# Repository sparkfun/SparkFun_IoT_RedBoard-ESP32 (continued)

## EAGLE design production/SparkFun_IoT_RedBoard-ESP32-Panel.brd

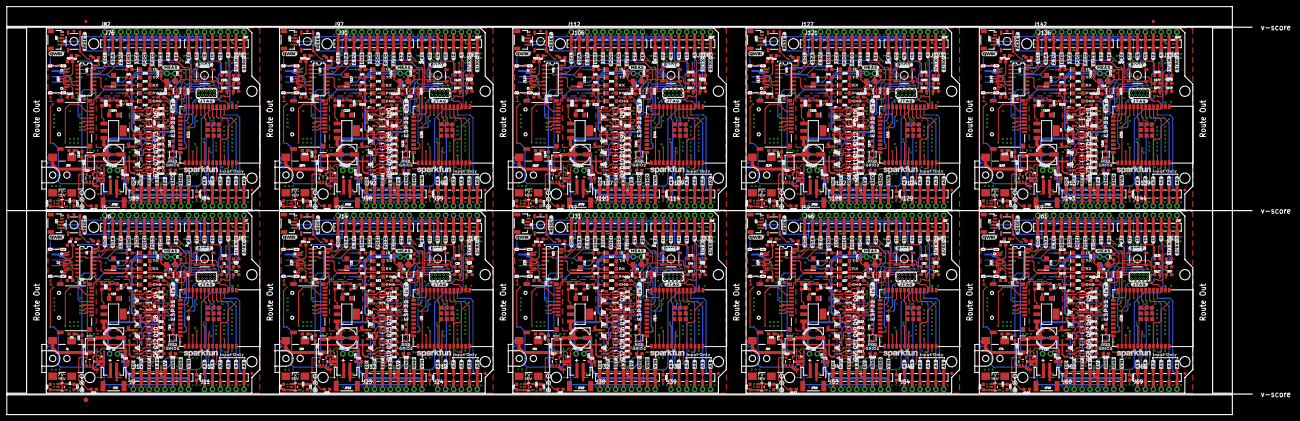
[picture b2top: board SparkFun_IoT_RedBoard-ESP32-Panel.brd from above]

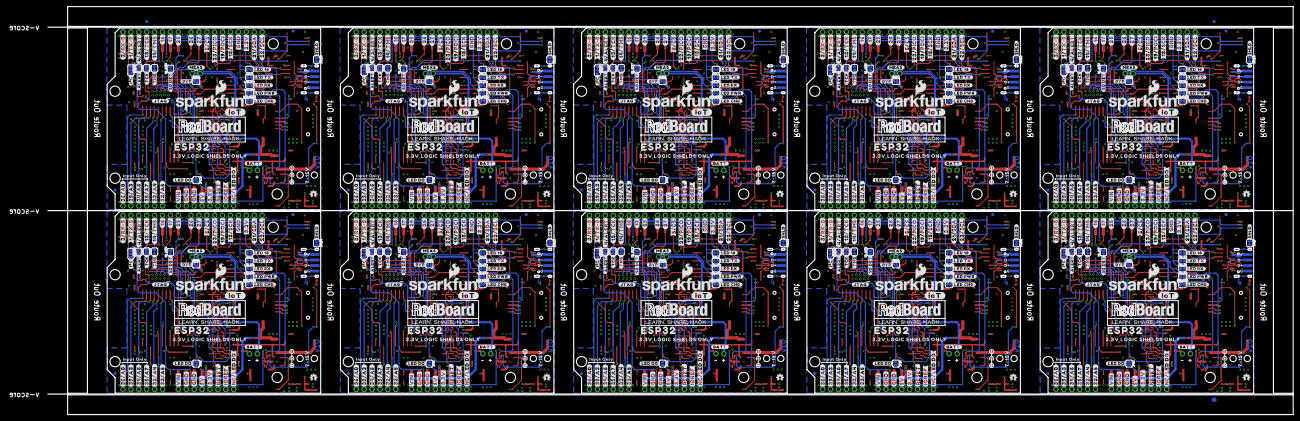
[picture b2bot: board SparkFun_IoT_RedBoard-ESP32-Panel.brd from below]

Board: 4 copper layers, 400.1 x 131.1 mm, 2336 parts (813 on the bottom side), 840 nets.

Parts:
!ALERT!, !ALERT!1, !ALERT!2, !ALERT!3, !ALERT!4, !ALERT!5, !ALERT!6, !ALERT!7, !ALERT!8, !ALERT!9: JUMPER-SMT_2_NO_SILK; SMT-JUMPER_2_NO_SILK
BYP, BYP1, BYP2, BYP3, BYP4, BYP5, BYP6, BYP7, BYP8, BYP9: JUMPER-SMT_2_NO_SILK; SMT-JUMPER_2_NO_SILK
C1, C2, C4, C5, C7, C11, C12, C13, C14, C17, C18, C20, C21, C24, C25, C26, C29, C31, C32, C35, C36, C37, C39, C40, C43, C44, C45, C48, C50, C51, C54, C55, C56, C58, C59, C62, C63, C64, C67, C69, C70, C73, C74, C75, C77, C78, C81, C82, C83, C86, C88, C89, C92, C93, C94, C96, C97, C100, C101, C102, C105, C107, C108, C111, C112, C113, C115, C116, C119, C120, C121, C124, C126, C127, C130, C131, C132, C134, C135, C138, C139, C140, C143, C145, C146, C149, C150, C151, C153, C154, C157, C158, C159, C162, C164, C165, C168, C169, C170, C172, C173, C176, C177, C178, C181, C183, C184, C187, C188, C189: 0.1uF; 0603
C3, C19, C27, C38, C46, C57, C65, C76, C84, C95, C103, C114, C122, C133, C141, C152, C160, C171, C179, C190: 10uF; 0603
C6, C10, C22, C28, C41, C47, C60, C66, C79, C85, C98, C104, C117, C123, C136, C142, C155, C161, C174, C180: 10uF; EIA3216
C8, C23, C42, C61, C80, C99, C118, C137, C156, C175: 10nF; 0603
C9, C30, C49, C68, C87, C106, C125, C144, C163, C182: 47uF; PANASONIC_D
C15, C16, C33, C34, C52, C53, C71, C72, C90, C91, C109, C110, C128, C129, C147, C148, C166, C167, C185, C186: 4.7uF; 0603
D1, D11, D18, D25, D32, D39, D46, D53, D60, D67: 3A/40V/500mV; SMA-DIODE
D2, D8, D15, D22, D29, D36, D43, D50, D57, D64: GREEN; LED-1206
D3, D4, D9, D12, D16, D19, D23, D26, D30, D33, D37, D40, D44, D47, D51, D54, D58, D61, D65, D68: Yellow; LED-1206
D5, D13, D20, D27, D34, D41, D48, D55, D62, D69: RED; LED-1206
D6, D10, D17, D24, D31, D38, D45, D52, D59, D66: BLUE; LED-1206
D7, D14, D21, D28, D35, D42, D49, D56, D63, D70: WS2812_2020; WS2812-2020
DOOT, DOOT1, DOOT2, DOOT3, DOOT4, DOOT5, DOOT6, DOOT7, DOOT8, DOOT9: GPIO0; TACTILE_SWITCH_SMD_5.2MM
E$1, E$2, E$3, E$4: FIDUCIAL-1X2
E$5, E$6: FIDUCIAL-1.5X3
F1, F2, F3, F4, F5, F6, F7, F8, F9, F10: 6V/0.75A/1.5A; 1206
I2C, I2C1, I2C2, I2C3, I2C4, I2C5, I2C6, I2C7, I2C8, I2C9: JUMPER-SMT_3_2-NC_TRACE_SILK; SMT-JUMPER_3_2-NC_TRACE_SILK
J1, J29, J44, J59, J74, J89, J104, J119, J134, J149: 5.5x2.1mm Barrel; POWER_JACK_SMD
J2, J20, J35, J50, J65, J80, J95, J110, J125, J140: USB-C; USB-C-16P-4LAYER-ISOLATED
J3, J21, J36, J51, J66, J81, J96, J111, J126, J141: USB_SOLDER_PADS; USB-SOLDER-PADS
J4, J26, J41, J56, J71, J86, J101, J116, J131, J146: 2X5_PTH_SILK_.05
J5, J22, J37, J52, J67, J82, J97, J112, J127, J142: M10NO_SILK; 1X10_NO_SILK
J6, J14, J31, J46, J61, J76, J91, J106, J121, J136: 1X10_SMD_COMBINED
J7, J9, J23, J25, J38, J40, J53, J55, J68, J70, J83, J85, J98, J100, J113, J115, J128, J130, J143, J145: 1X08_NO_SILK
J8, J10, J17, J18, J32, J33, J47, J48, J62, J63, J77, J78, J92, J93, J107, J108, J122, J123, J137, J138: 1X08_SMD_COMBINED
J11, J24, J39, J54, J69, J84, J99, J114, J129, J144: 1X06_NO_SILK
J12, J19, J34, J49, J64, J79, J94, J109, J124, J139: 1X06_SMD_STRAIGHT_COMBO
J13, J27, J42, J57, J72, J87, J102, J117, J132, J147: QWIIC_RIGHT_ANGLE; JST04_1MM_RA
J15, J28, J43, J58, J73, J88, J103, J118, J133, J148: MICRO-SD-PUSH-PUSH-EXT-PIN; MICROSD-EXTERNALPIN
J16, J30, J45, J60, J75, J90, J105, J120, J135, J150: 1X02_NO_SILK
JP1, JP7, JP8, JP9, JP15, JP16, JP17, JP18, JP25, JP26, JP27, JP28, JP35, JP36, JP37, JP38, JP45, JP46, JP47, JP48, JP55, JP56, JP57, JP58, JP65, JP66, JP67, JP68, JP75, JP76, JP77, JP78, JP85, JP86, JP87, JP88, JP95, JP96, JP97, JP98: FIDUCIAL1X2; FIDUCIAL-1X2
JP2, JP19, JP29, JP39, JP49, JP59, JP69, JP79, JP89, JP99: LiPo; JST-2-SMD
JP3, JP4, JP5, JP6, JP11, JP12, JP13, JP14, JP21, JP22, JP23, JP24, JP31, JP32, JP33, JP34, JP41, JP42, JP43, JP44, JP51, JP52, JP53, JP54, JP61, JP62, JP63, JP64, JP71, JP72, JP73, JP74, JP81, JP82, JP83, JP84, JP91, JP92, JP93, JP94: STAND-OFF
JP10, JP20, JP30, JP40, JP50, JP60, JP70, JP80, JP90, JP100: LED_DO; SMT-JUMPER_2_NO_SILK
LED_1, LED_2, LED_3, LED_4, LED_5, LED_6, LED_7, LED_8, LED_9, LED_18: JUMPER-SMT_2_NC_TRACE_SILK; SMT-JUMPER_2_NC_TRACE_SILK
LED_CHG, LED_CHG1, LED_CHG2, LED_CHG3, LED_CHG4, LED_CHG5, LED_CHG6, LED_CHG7, LED_CHG8, LED_CHG9: JUMPER-SMT_2_NC_TRACE_SILK; SMT-JUMPER_2_NC_TRACE_SILK
LED_PWR, LED_PWR1, LED_PWR2, LED_PWR3, LED_PWR4, LED_PWR5, LED_PWR6, LED_PWR7, LED_PWR8, LED_PWR9: JUMPER-SMT_2_NC_TRACE_SILK; SMT-JUMPER_2_NC_TRACE_SILK
LED_RX, LED_RX1, LED_RX2, LED_RX3, LED_RX4, LED_RX5, LED_RX6, LED_RX7, LED_RX8, LED_RX9: JUMPER-SMT_2_NC_TRACE_SILK; SMT-JUMPER_2_NC_TRACE_SILK
LED_TX, LED_TX1, LED_TX2, LED_TX3, LED_TX4, LED_TX5, LED_TX6, LED_TX7, LED_TX8, LED_TX9: JUMPER-SMT_2_NC_TRACE_SILK; SMT-JUMPER_2_NC_TRACE_SILK
LOGO1, LOGO4, LOGO9, LOGO13, LOGO17, LOGO21, LOGO25, LOGO29, LOGO33, LOGO37: SFE_LOGO_NAME.1_INCH; SFE_LOGO_NAME_.1
LOGO2, LOGO5, LOGO10, LOGO14, LOGO18, LOGO22, LOGO26, LOGO30, LOGO34, LOGO38: QWIIC_LOGO_5MM; QWIIC_5MM
LOGO3, LOGO7, LOGO11, LOGO15, LOGO19, LOGO23, LOGO27, LOGO31, LOGO35, LOGO39: OSHW-LOGOMINI; OSHW-LOGO-MINI
LOGO6, LOGO8, LOGO12, LOGO16, LOGO20, LOGO24, LOGO28, LOGO32, LOGO36, LOGO40: SFE_LOGO_NAME_FLAME.2_INCH; SFE_LOGO_NAME_FLAME_.2
MEAS, MEAS1, MEAS2, MEAS3, MEAS4, MEAS5, MEAS6, MEAS7, MEAS8, MEAS9: JUMPER-COMBO_2_NC_TRACE; COMBO-JUMPER_2_NC_TRACE
Q1, Q14, Q27, Q40, Q53, Q66, Q79, Q92, Q105, Q118: MBT3904DW1T1; SC70-6
Q2, Q17, Q30, Q43, Q56, Q69, Q82, Q95, Q108, Q121: SC70-6
Q3, Q5, Q7, Q9, Q11, Q13, Q16, Q18, Q20, Q22, Q24, Q26, Q29, Q31, Q33, Q35, Q37, Q39, Q42, Q44, Q46, Q48, Q50, Q52, Q55, Q57, Q59, Q61, Q63, Q65, Q68, Q70, Q72, Q74, Q76, Q78, Q81, Q83, Q85, Q87, Q89, Q91, Q94, Q96, Q98, Q100, Q102, Q104, Q107, Q109, Q111, Q113, Q115, Q117, Q120, Q122, Q124, Q126, Q128, Q130: 20V/4.2A/52mΩ/1.4W; SOT23-3
Q4, Q6, Q8, Q10, Q12, Q15, Q19, Q21, Q23, Q25, Q28, Q32, Q34, Q36, Q38, Q41, Q45, Q47, Q49, Q51, Q54, Q58, Q60, Q62, Q64, Q67, Q71, Q73, Q75, Q77, Q80, Q84, Q86, Q88, Q90, Q93, Q97, Q99, Q101, Q103, Q106, Q110, Q112, Q114, Q116, Q119, Q123, Q125, Q127, Q129: SOT363_PHILIPS
R1, R6, R7, R12, R13, R14, R15, R23, R35, R36, R37, R43, R45, R46, R47, R58, R65, R66, R67, R73, R75, R76, R77, R88, R95, R96, R97, R103, R105, R106, R107, R118, R125, R126, R127, R133, R135, R136, R137, R148, R155, R156, R157, R163, R165, R166, R167, R178, R185, R186, R187, R193, R195, R196, R197, R208, R215, R216, R217, R223, R225, R226, R227, R238, R245, R246, R247, R253, R255, R256, R257, R268, R275, R276, R277, R283, R285, R286, R287, R298: 10k; 0603
R2, R3, R33, R34, R63, R64, R93, R94, R123, R124, R153, R154, R183, R184, R213, R214, R243, R244, R273, R274: 5.1k; 0603
R4, R5, R21, R31, R32, R52, R61, R62, R82, R91, R92, R112, R121, R122, R142, R151, R152, R172, R181, R182, R202, R211, R212, R232, R241, R242, R262, R271, R272, R292: 1k; 0603
R8, R28, R29, R39, R40, R59, R69, R70, R89, R99, R100, R119, R129, R130, R149, R159, R160, R179, R189, R190, R209, R219, R220, R239, R249, R250, R269, R279, R280, R299: 2.2k; 0603
R9, R38, R68, R98, R128, R158, R188, R218, R248, R278: 4.7k; 0603
R10, R42, R72, R102, R132, R162, R192, R222, R252, R282: 240; 0603
R11, R41, R71, R101, R131, R161, R191, R221, R251, R281: 715; 0603
R16, R44, R74, R104, R134, R164, R194, R224, R254, R284: 47k; 0603
R17, R19, R24, R26, R48, R50, R54, R56, R78, R80, R84, R86, R108, R110, R114, R116, R138, R140, R144, R146, R168, R170, R174, R176, R198, R200, R204, R206, R228, R230, R234, R236, R258, R260, R264, R266, R288, R290, R294, R296: 100k; 0603
R18, R20, R25, R27, R49, R51, R55, R57, R79, R81, R85, R87, R109, R111, R115, R117, R139, R141, R145, R147, R169, R171, R175, R177, R199, R201, R205, R207, R229, R231, R235, R237, R259, R261, R265, R267, R289, R291, R295, R297: 1M; 0603
R22, R53, R83, R113, R143, R173, R203, R233, R263, R293: 2.0k; 0603
R30, R60, R90, R120, R150, R180, R210, R240, R270, R300: 100; 0603
S1, S2, S3, S4, S5, S6, S7, S8, S9, S10: Reset; TACTILE_SWITCH_SMD_5.2MM
SD_DET, SD_DET1, SD_DET2, SD_DET3, SD_DET4, SD_DET5, SD_DET6, SD_DET7, SD_DET8, SD_DET9: SD_DET; SMT-JUMPER_2_NO_SILK
SHLD, SHLD1, SHLD2, SHLD3, SHLD4, SHLD5, SHLD6, SHLD7, SHLD8, SHLD9: SHLD; SMT-JUMPER_2_NC_TRACE_SILK
TCK, TCK1, TCK2, TCK3, TCK4, TCK5, TCK6, TCK7, TCK8, TCK9: JUMPER-SMT_2_NC_TRACE_SILK; SMT-JUMPER_2_NC_TRACE_SILK
TMS, TMS1, TMS2, TMS3, TMS4, TMS5, TMS6, TMS7, TMS8, TMS9: JUMPER-SMT_2_NC_TRACE_SILK; SMT-JUMPER_2_NC_TRACE_SILK
TP1, TP2, TP3, TP4, TP5, TP6, TP7, TP8, TP9, TP10: TEST-POINT3; PAD.03X.03
U1, U8, U14, U20, U26, U32, U38, U44, U50, U56: ESP-WROOM-3232D; ESP-WROOM-32D
U2, U7, U13, U19, U25, U31, U37, U43, U49, U55: CH340C; SO016
U3, U9, U15, U21, U27, U33, U39, U45, U51, U57: LM1117; SOT223
U4, U10, U16, U22, U28, U34, U40, U46, U52, U58: XC6222B331MR-G; SOT23-5
U5, U11, U17, U23, U29, U35, U41, U47, U53, U59: MCP73831; SOT23-5
U6, U12, U18, U24, U30, U36, U42, U48, U54, U60: MAX17048; DFN-8
U$1, U$87, U$225, U$337, U$449, U$561, U$673, U$785, U$897, U$1009: V323252
U$2, U$3, U$226, U$338, U$450, U$562, U$674, U$786, U$898, U$1010: #SCL#34
U$4, U$95, U$227, U$339, U$451, U$563, U$675, U$787, U$899, U$1011: #SDA#33
U$5, U$116, U$228, U$340, U$452, U$564, U$676, U$788, U$900, U$1012: #3#3V#33
U$6, U$117, U$229, U$341, U$453, U$565, U$677, U$789, U$901, U$1013: #GND#32
U$7, U$118, U$230, U$342, U$454, U$566, U$678, U$790, U$902, U$1014: #SCK#31
U$8, U$119, U$231, U$343, U$455, U$567, U$679, U$791, U$903, U$1015: #POCI#30
U$9, U$120, U$232, U$344, U$456, U$568, U$680, U$792, U$904, U$1016: #PICO#29
U$10, U$121, U$233, U$345, U$457, U$569, U$681, U$793, U$905, U$1017: 1836
U$11, U$42, U$150, U$208, U$262, U$320, U$374, U$432, U$486, U$544, U$598, U$656, U$710, U$768, U$822, U$880, U$934, U$992, U$1046, U$1104: #MEAS#1851
U$12, U$122, U$234, U$346, U$458, U$570, U$682, U$794, U$906, U$1018: #27#27
U$13, U$123, U$235, U$347, U$459, U$571, U$683, U$795, U$907, U$1019: #26#26
U$14, U$124, U$236, U$348, U$460, U$572, U$684, U$796, U$908, U$1020: TX1838
U$15, U$125, U$237, U$349, U$461, U$573, U$685, U$797, U$909, U$1021: RX1839
U$16, U$126, U$238, U$350, U$462, U$574, U$686, U$798, U$910, U$1022: PWR1837
U$17, U$127, U$239, U$351, U$463, U$575, U$687, U$799, U$911, U$1023: CHG1840
U$18, U$128, U$240, U$352, U$464, U$576, U$688, U$800, U$912, U$1024: #25#18
U$19, U$129, U$241, U$353, U$465, U$577, U$689, U$801, U$913, U$1025: #17#17
U$20, U$130, U$242, U$354, U$466, U$578, U$690, U$802, U$914, U$1026: #16#15
U$21, U$131, U$243, U$355, U$467, U$579, U$691, U$803, U$915, U$1027: #14#14
U$22, U$132, U$244, U$356, U$468, U$580, U$692, U$804, U$916, U$1028: #13#5
U$23, U$133, U$245, U$357, U$469, U$581, U$693, U$805, U$917, U$1029: #4#2
U$24, U$202, U$314, U$426, U$538, U$650, U$762, U$874, U$986, U$1098: #3#RX#0#4
U$25, U$199, U$311, U$423, U$535, U$647, U$759, U$871, U$983, U$1095: #3#RX#0#0
U$26, U$134, U$246, U$358, U$470, U$582, U$694, U$806, U$918, U$1030: #RESET#1842
U$27, U$135, U$247, U$359, U$471, U$583, U$695, U$807, U$919, U$1031: #BOOT#1841
U$28, U$46, U$136, U$154, U$248, U$266, U$360, U$378, U$472, U$490, U$584, U$602, U$696, U$714, U$808, U$826, U$920, U$938, U$1032, U$1050: #JTAG#1847
U$29, U$137, U$249, U$361, U$473, U$585, U$697, U$809, U$921, U$1033: #A0#1843
U$30, U$138, U$250, U$362, U$474, U$586, U$698, U$810, U$922, U$1034: #A3#1843
U$31, U$139, U$251, U$363, U$475, U$587, U$699, U$811, U$923, U$1035: #A6#1843
U$32, U$140, U$252, U$364, U$476, U$588, U$700, U$812, U$924, U$1036: #A7#1843
U$33, U$141, U$253, U$365, U$477, U$589, U$701, U$813, U$925, U$1037: #A4#1843
U$34, U$142, U$254, U$366, U$478, U$590, U$702, U$814, U$926, U$1038: #A5#1843
U$35, U$143, U$255, U$367, U$479, U$591, U$703, U$815, U$927, U$1039: #VIN#1843
U$36, U$37, U$144, U$145, U$256, U$257, U$368, U$369, U$480, U$481, U$592, U$593, U$704, U$705, U$816, U$817, U$928, U$929, U$1040, U$1041: #GND#1844
U$38, U$146, U$258, U$370, U$482, U$594, U$706, U$818, U$930, U$1042: #5V#1845
U$39, U$147, U$259, U$371, U$483, U$595, U$707, U$819, U$931, U$1043: #3#3V#1845
U$40, U$148, U$260, U$372, U$484, U$596, U$708, U$820, U$932, U$1044: ##RST##1845
U$41, U$149, U$261, U$373, U$485, U$597, U$709, U$821, U$933, U$1045: #REF#1846
U$43, U$86, U$151, U$186, U$263, U$298, U$375, U$410, U$487, U$522, U$599, U$634, U$711, U$746, U$823, U$858, U$935, U$970, U$1047, U$1082: #1849
U$44, U$88, U$152, U$187, U$264, U$299, U$376, U$411, U$488, U$523, U$600, U$635, U$712, U$747, U$824, U$859, U$936, U$971, U$1048, U$1083: #1850
U$45, U$153, U$265, U$377, U$489, U$601, U$713, U$825, U$937, U$1049: #BATT#1848
U$47, U$196, U$308, U$420, U$532, U$644, U$756, U$868, U$980, U$1092: #IOT#132321874
U$48, U$155, U$267, U$379, U$491, U$603, U$715, U$827, U$939, U$1051: ESP321855
U$49, U$214, U$326, U$438, U$550, U$662, U$774, U$886, U$998, U$1110: #LED_18#0
U$50, U$156, U$268, U$380, U$492, U$604, U$716, U$828, U$940, U$1052: #39#A3#321862
U$51, U$157, U$269, U$381, U$493, U$605, U$717, U$829, U$941, U$1053: #36#A0#321862
U$52, U$220, U$332, U$444, U$556, U$668, U$780, U$892, U$1004, U$1116: #33#A5#0
U$53, U$158, U$270, U$382, U$494, U$606, U$718, U$830, U$942, U$1054: #35#A7#321862
U$54, U$159, U$271, U$383, U$495, U$607, U$719, U$831, U$943, U$1055: #32#A4#32321865
U$55, U$160, U$272, U$384, U$496, U$608, U$720, U$832, U$944, U$1056: #34#A6#321862
U$56, U$161, U$273, U$385, U$497, U$609, U$721, U$833, U$945, U$1057: #VIN#321862
U$57, U$60, U$162, U$165, U$274, U$277, U$386, U$389, U$498, U$501, U$610, U$613, U$722, U$725, U$834, U$837, U$946, U$949, U$1058, U$1061: #GND#321863
U$58, U$163, U$275, U$387, U$499, U$611, U$723, U$835, U$947, U$1059: #5V#321864
U$59, U$164, U$276, U$388, U$500, U$612, U$724, U$836, U$948, U$1060: #3#3V#321864
U$61, U$166, U$278, U$390, U$502, U$614, U$726, U$838, U$950, U$1062: ##RESET##321864
U$62, U$167, U$279, U$391, U$503, U$615, U$727, U$839, U$951, U$1063: #IOREF#321865
U$63, U$204, U$316, U$428, U$540, U$652, U$764, U$876, U$988, U$1100: #5##CS##0
U$64, U$205, U$317, U$429, U$541, U$653, U$765, U$877, U$989, U$1101: #BYP#0
U$65, U$207, U$319, U$431, U$543, U$655, U$767, U$879, U$991, U$1103: RGB0
U$66, U$168, U$280, U$392, U$504, U$616, U$728, U$840, U$952, U$1064: #13#TCK#32321869
U$67, U$169, U$281, U$393, U$505, U$617, U$729, U$841, U$953, U$1065: #14#TMS#32321869
U$68, U$170, U$282, U$394, U$506, U$618, U$730, U$842, U$954, U$1066: #16#32321869
U$69, U$171, U$283, U$395, U$507, U$619, U$731, U$843, U$955, U$1067: #17#32321869
U$70, U$172, U$284, U$396, U$508, U$620, U$732, U$844, U$956, U$1068: #25#32321869
U$71, U$173, U$285, U$397, U$509, U$621, U$733, U$845, U$957, U$1069: #26#32321869
U$72, U$174, U$286, U$398, U$510, U$622, U$734, U$846, U$958, U$1070: #5##CS##32321869
U$73, U$175, U$287, U$399, U$511, U$623, U$735, U$847, U$959, U$1071: #23#PICO#321866
U$74, U$176, U$288, U$400, U$512, U$624, U$736, U$848, U$960, U$1072: #19#POCI#321866
U$75, U$177, U$289, U$401, U$513, U$625, U$737, U$849, U$961, U$1073: #18#SCK#32321869
U$76, U$178, U$290, U$402, U$514, U$626, U$738, U$850, U$962, U$1074: #21#SDA#32321869
U$77, U$179, U$291, U$403, U$515, U$627, U$739, U$851, U$963, U$1075: #22#SCL#32321869
U$78, U$180, U$292, U$404, U$516, U$628, U$740, U$852, U$964, U$1076: #27#32321869
U$79, U$181, U$293, U$405, U$517, U$629, U$741, U$853, U$965, U$1077: #GND#321866
U$80, U$182, U$294, U$406, U$518, U$630, U$742, U$854, U$966, U$1078: #3#3V#321866
U$81, U$206, U$318, U$430, U$542, U$654, U$766, U$878, U$990, U$1102: #SHLD#0
U$82, U$221, U$333, U$445, U$557, U$669, U$781, U$893, U$1005, U$1117: #I�C#0
U$83, U$183, U$295, U$407, U$519, U$631, U$743, U$855, U$967, U$1079: D#32321863
U$84, U$184, U$296, U$408, U$520, U$632, U$744, U$856, U$968, U$1080: D#32321862
U$85, U$185, U$297, U$409, U$521, U$633, U$745, U$857, U$969, U$1081: G32321864
U$89, U$222, U$334, U$446, U$558, U$670, U$782, U$894, U$1006, U$1118: #DO#0
U$90, U$188, U$300, U$412, U$524, U$636, U$748, U$860, U$972, U$1084: ##ALERT##1852
U$91, U$189, U$301, U$413, U$525, U$637, U$749, U$861, U$973, U$1085: #TMS#1854
U$92, U$190, U$302, U$414, U$526, U$638, U$750, U$862, U$974, U$1086: #TCK#1853
U$93, U$195, U$307, U$419, U$531, U$643, U$755, U$867, U$979, U$1091: ESP32321856
U$94, U$99, U$209, U$210, U$321, U$322, U$433, U$434, U$545, U$546, U$657, U$658, U$769, U$770, U$881, U$882, U$993, U$994, U$1105, U$1106: POLARITY_MARKING_CENTER_POSITIVE#JPG
U$96, U$97, U$191, U$192, U$303, U$304, U$415, U$416, U$527, U$528, U$639, U$640, U$751, U$752, U$863, U$864, U$975, U$976, U$1087, U$1088: INPUT_ONLY321867
U$98, U$193, U$305, U$417, U$529, U$641, U$753, U$865, U$977, U$1089: REDBOARD_LOGO
U$100, U$194, U$306, U$418, U$530, U$642, U$754, U$866, U$978, U$1090: #IOT#132321869
U$101, U$197, U$309, U$421, U$533, U$645, U$757, U$869, U$981, U$1093: 7#15V32321861
U$102, U$201, U$313, U$425, U$537, U$649, U$761, U$873, U$985, U$1097: #4##ALERT##0
U$103, U$198, U$310, U$422, U$534, U$646, U$758, U$870, U$982, U$1094: 3#3V_LOGIC_SHIELDS_ONLY132321876
U$104, U$200, U$312, U$424, U$536, U$648, U$760, U$872, U$984, U$1096: #1#TX#0#0
U$105, U$203, U$315, U$427, U$539, U$651, U$763, U$875, U$987, U$1099: #1#TX#0#2
U$106, U$211, U$323, U$435, U$547, U$659, U$771, U$883, U$995, U$1107: 7V#0
U$107, U$212, U$324, U$436, U$548, U$660, U$772, U$884, U$996, U$1108: 15V0
U$108, U$213, U$325, U$437, U$549, U$661, U$773, U$885, U$997, U$1109: #SD_DET#0
U$109, U$215, U$327, U$439, U$551, U$663, U$775, U$887, U$999, U$1111: #LED_TX#0
U$110, U$216, U$328, U$440, U$552, U$664, U$776, U$888, U$1000, U$1112: #LED_RX#0
U$111, U$217, U$329, U$441, U$553, U$665, U$777, U$889, U$1001, U$1113: #LED_PWR#0
U$112, U$218, U$330, U$442, U$554, U$666, U$778, U$890, U$1002, U$1114: #LED_CHG#0
U$113, U$219, U$331, U$443, U$555, U$667, U$779, U$891, U$1003, U$1115: GPIO20
U$114, U$223, U$335, U$447, U$559, U$671, U$783, U$895, U$1007, U$1119: #LED_DO#1
U$115, U$224, U$336, U$448, U$560, U$672, U$784, U$896, U$1008, U$1120: #NC#LED_DO#0

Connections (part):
3.3V: C2.1, C3.1, C7.1, C13.1, C14.1, C19.1, D2.A, D3.A, D5.A, D7.VCC, I2C.2, J5.3, J6.3A, J6.3B, J9.2, J9.4, J10.2, J10.4, J13.2, J15.4, R1.2, R23.2, U1.2, U2.16, U4.5
3.3V1: C24.1, C26.1, C27.1, C31.1, C37.1, C38.1, D8.A, D9.A, D13.A, D14.VCC, I2C1.2, J14.3A, J14.3B, J17.2, J17.4, J22.3, J23.2, J23.4, J27.2, J28.4, R37.2, R58.2, U7.16, U8.2, U10.5
3.3V2: C43.1, C45.1, C46.1, C50.1, C56.1, C57.1, D15.A, D16.A, D20.A, D21.VCC, I2C2.2, J31.3A, J31.3B, J32.2, J32.4, J37.3, J38.2, J38.4, J42.2, J43.4, R67.2, R88.2, U13.16, U14.2, U16.5
3.3V3: C62.1, C64.1, C65.1, C69.1, C75.1, C76.1, D22.A, D23.A, D27.A, D28.VCC, I2C3.2, J46.3A, J46.3B, J47.2, J47.4, J52.3, J53.2, J53.4, J57.2, J58.4, R97.2, R118.2, U19.16, U20.2, U22.5
3.3V4: C81.1, C83.1, C84.1, C88.1, C94.1, C95.1, D29.A, D30.A, D34.A, D35.VCC, I2C4.2, J61.3A, J61.3B, J62.2, J62.4, J67.3, J68.2, J68.4, J72.2, J73.4, R127.2, R148.2, U25.16, U26.2, U28.5
3.3V5: C100.1, C102.1, C103.1, C107.1, C113.1, C114.1, D36.A, D37.A, D41.A, D42.VCC, I2C5.2, J76.3A, J76.3B, J77.2, J77.4, J82.3, J83.2, J83.4, J87.2, J88.4, R157.2, R178.2, U31.16, U32.2, U34.5
3.3V6: C119.1, C121.1, C122.1, C126.1, C132.1, C133.1, D43.A, D44.A, D48.A, D49.VCC, I2C6.2, J91.3A, J91.3B, J92.2, J92.4, J97.3, J98.2, J98.4, J102.2, J103.4, R187.2, R208.2, U37.16, U38.2, U40.5
3.3V7: C138.1, C140.1, C141.1, C145.1, C151.1, C152.1, D50.A, D51.A, D55.A, D56.VCC, I2C7.2, J106.3A, J106.3B, J107.2, J107.4, J112.3, J113.2, J113.4, J117.2, J118.4, R217.2, R238.2, U43.16, U44.2, U46.5
3.3V8: C157.1, C159.1, C160.1, C164.1, C170.1, C171.1, D57.A, D58.A, D62.A, D63.VCC, I2C8.2, J121.3A, J121.3B, J122.2, J122.4, J127.3, J128.2, J128.4, J132.2, J133.4, R247.2, R268.2, U49.16, U50.2, U52.5
3.3V9: C176.1, C178.1, C179.1, C183.1, C189.1, C190.1, D64.A, D65.A, D69.A, D70.VCC, I2C9.2, J136.3A, J136.3B, J137.2, J137.4, J142.3, J143.2, J143.4, J147.2, J148.4, R277.2, R298.2, U55.16, U56.2, U58.5
5V: BYP.2, C12.1, C18.1, F1.2, J9.5, J10.5, U4.1, U4.3
5V1: BYP1.2, C32.1, C36.1, F2.2, J17.5, J23.5, U10.1, U10.3
5V2: BYP2.2, C51.1, C55.1, F3.2, J32.5, J38.5, U16.1, U16.3
5V3: BYP3.2, C70.1, C74.1, F4.2, J47.5, J53.5, U22.1, U22.3
5V4: BYP4.2, C89.1, C93.1, F5.2, J62.5, J68.5, U28.1, U28.3
5V5: BYP5.2, C108.1, C112.1, F6.2, J77.5, J83.5, U34.1, U34.3
5V6: BYP6.2, C127.1, C131.1, F7.2, J92.5, J98.5, U40.1, U40.3
5V7: BYP7.2, C146.1, C150.1, F8.2, J107.5, J113.5, U46.1, U46.3
5V8: BYP8.2, C165.1, C169.1, F9.2, J122.5, J128.5, U52.1, U52.3
5V9: BYP9.2, C184.1, C188.1, F10.2, J137.5, J143.5, U58.1, U58.3
5V_CHG: C15.1, D4.A, Q10.4, Q11.2, Q12.4, Q13.2, U5.4
5V_CHG1: C34.1, D12.A, Q23.4, Q24.2, Q25.4, Q26.2, U11.4
5V_CHG2: C53.1, D19.A, Q36.4, Q37.2, Q38.4, Q39.2, U17.4
5V_CHG3: C72.1, D26.A, Q49.4, Q50.2, Q51.4, Q52.2, U23.4
5V_CHG4: C91.1, D33.A, Q62.4, Q63.2, Q64.4, Q65.2, U29.4
5V_CHG5: C110.1, D40.A, Q75.4, Q76.2, Q77.4, Q78.2, U35.4
5V_CHG6: C129.1, D47.A, Q88.4, Q89.2, Q90.4, Q91.2, U41.4
5V_CHG7: C148.1, D54.A, Q101.4, Q102.2, Q103.4, Q104.2, U47.4
5V_CHG8: C167.1, D61.A, Q114.4, Q115.2, Q116.4, Q117.2, U53.4
5V_CHG9: C186.1, D68.A, Q127.4, Q128.2, Q129.4, Q130.2, U59.4
5V_EXT: C10.+, C11.1, Q6.1, Q7.3, Q12.1, Q13.3, R10.2, R12.1, U3.2, U3.4
5V_EXT1: C28.+, C29.1, Q19.1, Q20.3, Q25.1, Q26.3, R42.2, R47.1, U9.2, U9.4
5V_EXT2: C47.+, C48.1, Q32.1, Q33.3, Q38.1, Q39.3, R72.2, R77.1, U15.2, U15.4
5V_EXT3: C66.+, C67.1, Q45.1, Q46.3, Q51.1, Q52.3, R102.2, R107.1, U21.2, U21.4
5V_EXT4: C85.+, C86.1, Q58.1, Q59.3, Q64.1, Q65.3, R132.2, R137.1, U27.2, U27.4
5V_EXT5: C104.+, C105.1, Q71.1, Q72.3, Q77.1, Q78.3, R162.2, R167.1, U33.2, U33.4
5V_EXT6: C123.+, C124.1, Q84.1, Q85.3, Q90.1, Q91.3, R192.2, R197.1, U39.2, U39.4
5V_EXT7: C142.+, C143.1, Q97.1, Q98.3, Q103.1, Q104.3, R222.2, R227.1, U45.2, U45.4
5V_EXT8: C161.+, C162.1, Q110.1, Q111.3, Q116.1, Q117.3, R252.2, R257.1, U51.2, U51.4
5V_EXT9: C180.+, C181.1, Q123.1, Q124.3, Q129.1, Q130.3, R282.2, R287.1, U57.2, U57.4
5V_MEAS: MEAS.1, MEAS.3, Q4.4, Q5.2, Q6.4, Q7.2, Q8.4, Q9.2
5V_MEAS1: MEAS1.1, MEAS1.3, Q15.4, Q16.2, Q19.4, Q20.2, Q21.4, Q22.2
5V_MEAS2: MEAS2.1, MEAS2.3, Q28.4, Q29.2, Q32.4, Q33.2, Q34.4, Q35.2
5V_MEAS3: MEAS3.1, MEAS3.3, Q41.4, Q42.2, Q45.4, Q46.2, Q47.4, Q48.2
5V_MEAS4: MEAS4.1, MEAS4.3, Q54.4, Q55.2, Q58.4, Q59.2, Q60.4, Q61.2
5V_MEAS5: MEAS5.1, MEAS5.3, Q67.4, Q68.2, Q71.4, Q72.2, Q73.4, Q74.2
5V_MEAS6: MEAS6.1, MEAS6.3, Q80.4, Q81.2, Q84.4, Q85.2, Q86.4, Q87.2
5V_MEAS7: MEAS7.1, MEAS7.3, Q93.4, Q94.2, Q97.4, Q98.2, Q99.4, Q100.2
5V_MEAS8: MEAS8.1, MEAS8.3, Q106.4, Q107.2, Q110.4, Q111.2, Q112.4, Q113.2
5V_MEAS9: MEAS9.1, MEAS9.3, Q119.4, Q120.2, Q123.4, Q124.2, Q125.4, Q126.2
!DTR!: Q1.4, R6.1, U2.13
!DTR!1: Q14.4, R36.1, U7.13
!DTR!2: Q27.4, R66.1, U13.13
!DTR!3: Q40.4, R96.1, U19.13
!DTR!4: Q53.4, R126.1, U25.13
!DTR!5: Q66.4, R156.1, U31.13
!DTR!6: Q79.4, R186.1, U37.13
!DTR!7: Q92.4, R216.1, U43.13
!DTR!8: Q105.4, R246.1, U49.13
!DTR!9: Q118.4, R276.1, U55.13
!GAUGE_ALERT!: !ALERT!.1, R23.1, U6.5
!GAUGE_ALERT!1: !ALERT!1.1, R58.1, U12.5
!GAUGE_ALERT!2: !ALERT!2.1, R88.1, U18.5
!GAUGE_ALERT!3: !ALERT!3.1, R118.1, U24.5
!GAUGE_ALERT!4: !ALERT!4.1, R148.1, U30.5
!GAUGE_ALERT!5: !ALERT!5.1, R178.1, U36.5
!GAUGE_ALERT!6: !ALERT!6.1, R208.1, U42.5
!GAUGE_ALERT!7: !ALERT!7.1, R238.1, U48.5
!GAUGE_ALERT!8: !ALERT!8.1, R268.1, U54.5
!GAUGE_ALERT!9: !ALERT!9.1, R298.1, U60.5
!RTS!: Q1.1, R7.1, U2.14
!RTS!1: Q14.1, R35.1, U7.14
!RTS!2: Q27.1, R65.1, U13.14
!RTS!3: Q40.1, R95.1, U19.14
!RTS!4: Q53.1, R125.1, U25.14
!RTS!5: Q66.1, R155.1, U31.14
!RTS!6: Q79.1, R185.1, U37.14
!RTS!7: Q92.1, R215.1, U43.14
!RTS!8: Q105.1, R245.1, U49.14
!RTS!9: Q118.1, R275.1, U55.14
CC1: J2.A5, R3.2
CC2: J2.B5, R2.2
CC3: J20.B5, R33.2
CC4: J20.A5, R34.2
CC5: J35.B5, R63.2
CC6: J35.A5, R64.2
CC7: J50.B5, R93.2
CC8: J50.A5, R94.2
CC9: J65.B5, R123.2
CC10: J65.A5, R124.2
CC11: J80.B5, R153.2
CC12: J80.A5, R154.2
CC13: J95.B5, R183.2
CC14: J95.A5, R184.2
CC15: J110.B5, R213.2
CC16: J110.A5, R214.2
CC17: J125.B5, R243.2
CC18: J125.A5, R244.2
CC19: J140.B5, R273.2
CC20: J140.A5, R274.2
D+: J2.A6, J2.B6, J3.D+, U2.5
D+1: J20.A6, J20.B6, J21.D+, U7.5
D+2: J35.A6, J35.B6, J36.D+, U13.5
D+3: J50.A6, J50.B6, J51.D+, U19.5
D+4: J65.A6, J65.B6, J66.D+, U25.5
D+5: J80.A6, J80.B6, J81.D+, U31.5
D+6: J95.A6, J95.B6, J96.D+, U37.5
D+7: J110.A6, J110.B6, J111.D+, U43.5
D+8: J125.A6, J125.B6, J126.D+, U49.5
D+9: J140.A6, J140.B6, J141.D+, U55.5
D-: J2.A7, J2.B7, J3.D-, U2.6
D-1: J20.A7, J20.B7, J21.D-, U7.6
D-2: J35.A7, J35.B7, J36.D-, U13.6
D-3: J50.A7, J50.B7, J51.D-, U19.6
D-4: J65.A7, J65.B7, J66.D-, U25.6
D-5: J80.A7, J80.B7, J81.D-, U31.6
D-6: J95.A7, J95.B7, J96.D-, U37.6
D-7: J110.A7, J110.B7, J111.D-, U43.6
D-8: J125.A7, J125.B7, J126.D-, U49.6
D-9: J140.A7, J140.B7, J141.D-, U55.6
ESP32_0: DOOT.3, DOOT.4, Q1.3, U1.25
ESP32_1: DOOT1.3, DOOT1.4, Q14.3, U8.25
ESP32_2: DOOT2.3, DOOT2.4, Q27.3, U14.25
ESP32_3: DOOT3.3, DOOT3.4, Q40.3, U20.25
ESP32_4: DOOT4.3, DOOT4.4, Q53.3, U26.25
ESP32_5: DOOT5.3, DOOT5.4, Q66.3, U32.25
ESP32_6: DOOT6.3, DOOT6.4, Q79.3, U38.25
ESP32_7: DOOT7.3, DOOT7.4, Q92.3, U44.25
ESP32_8: DOOT8.3, DOOT8.4, Q105.3, U50.25
ESP32_9: DOOT9.3, DOOT9.4, Q118.3, U56.25
ESP32_ADC0: J11.6, J12.6, U1.4
ESP32_ADC1: J19.6, J24.6, U8.4
ESP32_ADC2: J19.5, J24.5, U8.5
ESP32_ADC3: J11.5, J12.5, U1.5
ESP32_ADC4: J11.2, J12.2, U1.8
ESP32_ADC5: J11.1, J12.1, U1.9
ESP32_ADC6: J11.4, J12.4, U1.6
ESP32_ADC7: J11.3, J12.3, U1.7
ESP32_ADC8: J19.4, J24.4, U8.6
ESP32_ADC9: J19.3, J24.3, U8.7
ESP32_ADC10: J19.1, J24.1, U8.9
ESP32_ADC11: J19.2, J24.2, U8.8
ESP32_ADC12: J34.6, J39.6, U14.4
ESP32_ADC13: J34.5, J39.5, U14.5
ESP32_ADC14: J34.4, J39.4, U14.6
ESP32_ADC15: J34.3, J39.3, U14.7
ESP32_ADC16: J34.1, J39.1, U14.9
ESP32_ADC17: J34.2, J39.2, U14.8
ESP32_ADC18: J49.6, J54.6, U20.4
ESP32_ADC19: J49.5, J54.5, U20.5
ESP32_ADC20: J49.4, J54.4, U20.6
ESP32_ADC21: J49.3, J54.3, U20.7
ESP32_ADC22: J49.1, J54.1, U20.9
ESP32_ADC23: J49.2, J54.2, U20.8
ESP32_ADC24: J64.6, J69.6, U26.4
ESP32_ADC25: J64.5, J69.5, U26.5
ESP32_ADC26: J64.4, J69.4, U26.6
ESP32_ADC27: J64.3, J69.3, U26.7
ESP32_ADC28: J64.1, J69.1, U26.9
ESP32_ADC29: J64.2, J69.2, U26.8
ESP32_ADC30: J79.6, J84.6, U32.4
ESP32_ADC31: J79.5, J84.5, U32.5
ESP32_ADC32: J79.4, J84.4, U32.6
ESP32_ADC33: J79.3, J84.3, U32.7
ESP32_ADC34: J79.1, J84.1, U32.9
ESP32_ADC35: J79.2, J84.2, U32.8
ESP32_ADC36: J94.6, J99.6, U38.4
ESP32_ADC37: J94.5, J99.5, U38.5
ESP32_ADC38: J94.4, J99.4, U38.6
ESP32_ADC39: J94.3, J99.3, U38.7
ESP32_ADC40: J94.1, J99.1, U38.9
ESP32_ADC41: J94.2, J99.2, U38.8
ESP32_ADC42: J109.6, J114.6, U44.4
ESP32_ADC43: J109.5, J114.5, U44.5
ESP32_ADC44: J109.4, J114.4, U44.6
ESP32_ADC45: J109.3, J114.3, U44.7
ESP32_ADC46: J109.1, J114.1, U44.9
ESP32_ADC47: J109.2, J114.2, U44.8
ESP32_ADC48: J124.6, J129.6, U50.4
ESP32_ADC49: J124.5, J129.5, U50.5
ESP32_ADC50: J124.4, J129.4, U50.6
ESP32_ADC51: J124.3, J129.3, U50.7
ESP32_ADC52: J124.1, J129.1, U50.9
ESP32_ADC53: J124.2, J129.2, U50.8
ESP32_ADC54: J139.6, J144.6, U56.4
ESP32_ADC55: J139.5, J144.5, U56.5
ESP32_ADC56: J139.4, J144.4, U56.6
ESP32_ADC57: J139.3, J144.3, U56.7
ESP32_ADC58: J139.1, J144.1, U56.9
ESP32_ADC59: J139.2, J144.2, U56.8
ESP32_EN: C1.1, J9.3, J10.3, Q1.6, R1.1, S1.3, S1.4, U1.3
ESP32_EN1: C25.1, J17.3, J23.3, Q14.6, R37.1, S2.3, S2.4, U8.3
ESP32_EN2: C44.1, J32.3, J38.3, Q27.6, R67.1, S3.3, S3.4, U14.3
ESP32_EN3: C63.1, J47.3, J53.3, Q40.6, R97.1, S4.3, S4.4, U20.3
ESP32_EN4: C82.1, J62.3, J68.3, Q53.6, R127.1, S5.3, S5.4, U26.3
ESP32_EN5: C101.1, J77.3, J83.3, Q66.6, R157.1, S6.3, S6.4, U32.3
ESP32_EN6: C120.1, J92.3, J98.3, Q79.6, R187.1, S7.3, S7.4, U38.3
ESP32_EN7: C139.1, J107.3, J113.3, Q92.6, R217.1, S8.3, S8.4, U44.3
ESP32_EN8: C158.1, J122.3, J128.3, Q105.6, R247.1, S9.3, S9.4, U50.3
ESP32_EN9: C177.1, J137.3, J143.3, Q118.6, R277.1, S10.3, S10.4, U56.3
ESP32_GPIO1: D14.DI, U8.24
ESP32_GPIO2: D7.DI, U1.24
ESP32_GPIO3: !ALERT!1.2, J18.3, J25.3, U8.26
ESP32_GPIO4: !ALERT!.2, J7.3, J8.3, U1.26
ESP32_GPIO5: J18.7, J25.7, U8.28
ESP32_GPIO5_!CS!: J5.8, J6.8A, J6.8B, J15.2, U1.29
ESP32_GPIO5_!CS!1: J14.8A, J14.8B, J22.8, J28.2, U8.29
ESP32_GPIO5_!CS!2: J31.8A, J31.8B, J37.8, J43.2, U14.29
ESP32_GPIO5_!CS!3: J46.8A, J46.8B, J52.8, J58.2, U20.29
ESP32_GPIO5_!CS!4: J61.8A, J61.8B, J67.8, J73.2, U26.29
ESP32_GPIO5_!CS!5: J76.8A, J76.8B, J82.8, J88.2, U32.29
ESP32_GPIO5_!CS!6: J91.8A, J91.8B, J97.8, J103.2, U38.29
ESP32_GPIO5_!CS!7: J106.8A, J106.8B, J112.8, J118.2, U44.29
ESP32_GPIO5_!CS!8: J121.8A, J121.8B, J127.8, J133.2, U50.29
ESP32_GPIO5_!CS!9: J136.8A, J136.8B, J142.8, J148.2, U56.29
ESP32_GPIO6: J18.8, J25.8, U8.10
ESP32_GPIO7: J14.10A, J14.10B, J22.10, U8.11
ESP32_GPIO8: J14.9A, J14.9B, J22.9, U8.12
ESP32_GPIO9: J18.6, J25.6, SD_DET1.2, U8.27
ESP32_GPIO10: D21.DI, U14.24
ESP32_GPIO11: !ALERT!2.2, J33.3, J40.3, U14.26
ESP32_GPIO12: J33.7, J40.7, U14.28
ESP32_GPIO12_TDI: J4.8, TP1.1, U1.14
ESP32_GPIO12_TDI1: J26.8, TP2.1, U8.14
ESP32_GPIO12_TDI2: J41.8, TP3.1, U14.14
ESP32_GPIO12_TDI3: J56.8, TP4.1, U20.14
ESP32_GPIO12_TDI4: J71.8, TP5.1, U26.14
ESP32_GPIO12_TDI5: J86.8, TP6.1, U32.14
ESP32_GPIO12_TDI6: J101.8, TP7.1, U38.14
ESP32_GPIO12_TDI7: J116.8, TP8.1, U44.14
ESP32_GPIO12_TDI8: J131.8, TP9.1, U50.14
ESP32_GPIO12_TDI9: J146.8, TP10.1, U56.14
ESP32_GPIO13: J33.8, J40.8, U14.10
ESP32_GPIO13_HDR: J7.4, J8.4, TCK.2
ESP32_GPIO13_HDR1: J18.4, J25.4, TCK1.2
ESP32_GPIO13_HDR2: J33.4, J40.4, TCK2.2
ESP32_GPIO13_HDR3: J48.4, J55.4, TCK3.2
ESP32_GPIO13_HDR4: J63.4, J70.4, TCK4.2
ESP32_GPIO13_HDR5: J78.4, J85.4, TCK5.2
ESP32_GPIO13_HDR6: J93.4, J100.4, TCK6.2
ESP32_GPIO13_HDR7: J108.4, J115.4, TCK7.2
ESP32_GPIO13_HDR8: J123.4, J130.4, TCK8.2
ESP32_GPIO13_HDR9: J138.4, J145.4, TCK9.2
ESP32_GPIO13_TCK: J4.4, TCK.1, U1.16
ESP32_GPIO13_TCK1: J26.4, TCK1.1, U8.16
ESP32_GPIO13_TCK2: J41.4, TCK2.1, U14.16
ESP32_GPIO13_TCK3: J56.4, TCK3.1, U20.16
ESP32_GPIO13_TCK4: J71.4, TCK4.1, U26.16
ESP32_GPIO13_TCK5: J86.4, TCK5.1, U32.16
ESP32_GPIO13_TCK6: J101.4, TCK6.1, U38.16
ESP32_GPIO13_TCK7: J116.4, TCK7.1, U44.16
ESP32_GPIO13_TCK8: J131.4, TCK8.1, U50.16
ESP32_GPIO13_TCK9: J146.4, TCK9.1, U56.16
ESP32_GPIO14: J31.10A, J31.10B, J37.10, U14.11
ESP32_GPIO14_HDR: J7.5, J8.5, TMS.2
ESP32_GPIO14_HDR1: J18.5, J25.5, TMS1.2
ESP32_GPIO14_HDR2: J33.5, J40.5, TMS2.2
ESP32_GPIO14_HDR3: J48.5, J55.5, TMS3.2
ESP32_GPIO14_HDR4: J63.5, J70.5, TMS4.2
ESP32_GPIO14_HDR5: J78.5, J85.5, TMS5.2
ESP32_GPIO14_HDR6: J93.5, J100.5, TMS6.2
ESP32_GPIO14_HDR7: J108.5, J115.5, TMS7.2
ESP32_GPIO14_HDR8: J123.5, J130.5, TMS8.2
ESP32_GPIO14_HDR9: J138.5, J145.5, TMS9.2
ESP32_GPIO14_TMS: J4.2, TMS.1, U1.13
ESP32_GPIO14_TMS1: J26.2, TMS1.1, U8.13
ESP32_GPIO14_TMS2: J41.2, TMS2.1, U14.13
ESP32_GPIO14_TMS3: J56.2, TMS3.1, U20.13
ESP32_GPIO14_TMS4: J71.2, TMS4.1, U26.13
ESP32_GPIO14_TMS5: J86.2, TMS5.1, U32.13
ESP32_GPIO14_TMS6: J101.2, TMS6.1, U38.13
ESP32_GPIO14_TMS7: J116.2, TMS7.1, U44.13
ESP32_GPIO14_TMS8: J131.2, TMS8.1, U50.13
ESP32_GPIO14_TMS9: J146.2, TMS9.1, U56.13
ESP32_GPIO15: J31.9A, J31.9B, J37.9, U14.12
ESP32_GPIO15_TDO: J4.6, U1.23
ESP32_GPIO15_TDO1: J26.6, U8.23
ESP32_GPIO15_TDO2: J41.6, U14.23
ESP32_GPIO15_TDO3: J56.6, U20.23
ESP32_GPIO15_TDO4: J71.6, U26.23
ESP32_GPIO15_TDO5: J86.6, U32.23
ESP32_GPIO15_TDO6: J101.6, U38.23
ESP32_GPIO15_TDO7: J116.6, U44.23
ESP32_GPIO15_TDO8: J131.6, U50.23
ESP32_GPIO15_TDO9: J146.6, U56.23
ESP32_GPIO16: J7.6, J8.6, SD_DET.2, U1.27
ESP32_GPIO17: J7.7, J8.7, U1.28
ESP32_GPIO18: J33.6, J40.6, SD_DET2.2, U14.27
ESP32_GPIO18_SCK: D6.A, J5.5, J6.5A, J6.5B, J15.5, U1.30
ESP32_GPIO18_SCK1: D10.A, J14.5A, J14.5B, J22.5, J28.5, U8.30
ESP32_GPIO18_SCK2: D17.A, J31.5A, J31.5B, J37.5, J43.5, U14.30
ESP32_GPIO18_SCK3: D24.A, J46.5A, J46.5B, J52.5, J58.5, U20.30
ESP32_GPIO18_SCK4: D31.A, J61.5A, J61.5B, J67.5, J73.5, U26.30
ESP32_GPIO18_SCK5: D38.A, J76.5A, J76.5B, J82.5, J88.5, U32.30
ESP32_GPIO18_SCK6: D45.A, J91.5A, J91.5B, J97.5, J103.5, U38.30
ESP32_GPIO18_SCK7: D52.A, J106.5A, J106.5B, J112.5, J118.5, U44.30
ESP32_GPIO18_SCK8: D59.A, J121.5A, J121.5B, J127.5, J133.5, U50.30
ESP32_GPIO18_SCK9: D66.A, J136.5A, J136.5B, J142.5, J148.5, U56.30
ESP32_GPIO19: D28.DI, U20.24
ESP32_GPIO19_POCI: J5.6, J6.6A, J6.6B, J15.7, U1.31
ESP32_GPIO19_POCI1: J14.6A, J14.6B, J22.6, J28.7, U8.31
ESP32_GPIO19_POCI2: J31.6A, J31.6B, J37.6, J43.7, U14.31
ESP32_GPIO19_POCI3: J46.6A, J46.6B, J52.6, J58.7, U20.31
ESP32_GPIO19_POCI4: J61.6A, J61.6B, J67.6, J73.7, U26.31
ESP32_GPIO19_POCI5: J76.6A, J76.6B, J82.6, J88.7, U32.31
ESP32_GPIO19_POCI6: J91.6A, J91.6B, J97.6, J103.7, U38.31
ESP32_GPIO19_POCI7: J106.6A, J106.6B, J112.6, J118.7, U44.31
ESP32_GPIO19_POCI8: J121.6A, J121.6B, J127.6, J133.7, U50.31
ESP32_GPIO19_POCI9: J136.6A, J136.6B, J142.6, J148.7, U56.31
ESP32_GPIO20: !ALERT!3.2, J48.3, J55.3, U20.26
ESP32_GPIO21: J48.7, J55.7, U20.28
ESP32_GPIO22: J48.8, J55.8, U20.10
ESP32_GPIO23: J46.10A, J46.10B, J52.10, U20.11
ESP32_GPIO23_PICO: J5.7, J6.7A, J6.7B, J15.3, U1.37
ESP32_GPIO23_PICO1: J14.7A, J14.7B, J22.7, J28.3, U8.37
ESP32_GPIO23_PICO2: J31.7A, J31.7B, J37.7, J43.3, U14.37
ESP32_GPIO23_PICO3: J46.7A, J46.7B, J52.7, J58.3, U20.37
ESP32_GPIO23_PICO4: J61.7A, J61.7B, J67.7, J73.3, U26.37
ESP32_GPIO23_PICO5: J76.7A, J76.7B, J82.7, J88.3, U32.37
ESP32_GPIO23_PICO6: J91.7A, J91.7B, J97.7, J103.3, U38.37
ESP32_GPIO23_PICO7: J106.7A, J106.7B, J112.7, J118.3, U44.37
ESP32_GPIO23_PICO8: J121.7A, J121.7B, J127.7, J133.3, U50.37
ESP32_GPIO23_PICO9: J136.7A, J136.7B, J142.7, J148.3, U56.37
ESP32_GPIO24: J46.9A, J46.9B, J52.9, U20.12
ESP32_GPIO25: J7.8, J8.8, U1.10
ESP32_GPIO26: J5.10, J6.10A, J6.10B, U1.11
ESP32_GPIO27: J5.9, J6.9A, J6.9B, U1.12
ESP32_GPIO28: J48.6, J55.6, SD_DET3.2, U20.27
ESP32_GPIO29: D35.DI, U26.24
ESP32_GPIO30: !ALERT!4.2, J63.3, J70.3, U26.26
ESP32_GPIO31: J63.7, J70.7, U26.28
ESP32_GPIO32: J63.8, J70.8, U26.10
ESP32_GPIO33: J61.10A, J61.10B, J67.10, U26.11
ESP32_GPIO34: J61.9A, J61.9B, J67.9, U26.12
ESP32_GPIO35: J63.6, J70.6, SD_DET4.2, U26.27
ESP32_GPIO36: D42.DI, U32.24
ESP32_GPIO37: !ALERT!5.2, J78.3, J85.3, U32.26
ESP32_GPIO38: J78.7, J85.7, U32.28
ESP32_GPIO39: J78.8, J85.8, U32.10
ESP32_GPIO40: J76.10A, J76.10B, J82.10, U32.11
ESP32_GPIO41: J76.9A, J76.9B, J82.9, U32.12
ESP32_GPIO42: J78.6, J85.6, SD_DET5.2, U32.27
ESP32_GPIO43: D49.DI, U38.24
ESP32_GPIO44: !ALERT!6.2, J93.3, J100.3, U38.26
ESP32_GPIO45: J93.7, J100.7, U38.28
ESP32_GPIO46: J93.8, J100.8, U38.10
ESP32_GPIO47: J91.10A, J91.10B, J97.10, U38.11
ESP32_GPIO48: J91.9A, J91.9B, J97.9, U38.12
ESP32_GPIO49: J93.6, J100.6, SD_DET6.2, U38.27
ESP32_GPIO50: D56.DI, U44.24
ESP32_GPIO51: !ALERT!7.2, J108.3, J115.3, U44.26
ESP32_GPIO52: J108.7, J115.7, U44.28
ESP32_GPIO53: J108.8, J115.8, U44.10
ESP32_GPIO54: J106.10A, J106.10B, J112.10, U44.11
ESP32_GPIO55: J106.9A, J106.9B, J112.9, U44.12
ESP32_GPIO56: J108.6, J115.6, SD_DET7.2, U44.27
ESP32_GPIO57: D63.DI, U50.24
ESP32_GPIO58: !ALERT!8.2, J123.3, J130.3, U50.26
ESP32_GPIO59: J123.7, J130.7, U50.28
ESP32_GPIO60: J123.8, J130.8, U50.10
ESP32_GPIO61: J121.10A, J121.10B, J127.10, U50.11
ESP32_GPIO62: J121.9A, J121.9B, J127.9, U50.12
ESP32_GPIO63: J123.6, J130.6, SD_DET8.2, U50.27
ESP32_GPIO64: D70.DI, U56.24
ESP32_GPIO65: !ALERT!9.2, J138.3, J145.3, U56.26
ESP32_GPIO66: J138.7, J145.7, U56.28
ESP32_GPIO67: J138.8, J145.8, U56.10
ESP32_GPIO68: J136.10A, J136.10B, J142.10, U56.11
ESP32_GPIO69: J136.9A, J136.9B, J142.9, U56.12
ESP32_GPIO70: J138.6, J145.6, SD_DET9.2, U56.27
ESP32_RXD0: J7.1, J8.1, LED_RX.1, U1.34, U2.2
ESP32_RXD1: J18.1, J25.1, LED_RX1.1, U7.2, U8.34
ESP32_RXD2: J33.1, J40.1, LED_RX2.1, U13.2, U14.34
ESP32_RXD3: J48.1, J55.1, LED_RX3.1, U19.2, U20.34
ESP32_RXD4: J63.1, J70.1, LED_RX4.1, U25.2, U26.34
ESP32_RXD5: J78.1, J85.1, LED_RX5.1, U31.2, U32.34
ESP32_RXD6: J93.1, J100.1, LED_RX6.1, U37.2, U38.34
ESP32_RXD7: J108.1, J115.1, LED_RX7.1, U43.2, U44.34
ESP32_RXD8: J123.1, J130.1, LED_RX8.1, U49.2, U50.34
ESP32_RXD9: J138.1, J145.1, LED_RX9.1, U55.2, U56.34
ESP32_SCL: J5.1, J6.1A, J6.1B, J13.4, R28.1, U1.36, U6.7
ESP32_SCL1: J14.1A, J14.1B, J22.1, J27.4, R39.1, U8.36, U12.7
ESP32_SCL2: J31.1A, J31.1B, J37.1, J42.4, R69.1, U14.36, U18.7
ESP32_SCL3: J46.1A, J46.1B, J52.1, J57.4, R99.1, U20.36, U24.7
ESP32_SCL4: J61.1A, J61.1B, J67.1, J72.4, R129.1, U26.36, U30.7
ESP32_SCL5: J76.1A, J76.1B, J82.1, J87.4, R159.1, U32.36, U36.7
ESP32_SCL6: J91.1A, J91.1B, J97.1, J102.4, R189.1, U38.36, U42.7
ESP32_SCL7: J106.1A, J106.1B, J112.1, J117.4, R219.1, U44.36, U48.7
ESP32_SCL8: J121.1A, J121.1B, J127.1, J132.4, R249.1, U50.36, U54.7
ESP32_SCL9: J136.1A, J136.1B, J142.1, J147.4, R279.1, U56.36, U60.7
ESP32_SDA: J5.2, J6.2A, J6.2B, J13.3, R29.1, U1.33, U6.8
ESP32_SDA1: J14.2A, J14.2B, J22.2, J27.3, R40.1, U8.33, U12.8
ESP32_SDA2: J31.2A, J31.2B, J37.2, J42.3, R70.1, U14.33, U18.8
ESP32_SDA3: J46.2A, J46.2B, J52.2, J57.3, R100.1, U20.33, U24.8
ESP32_SDA4: J61.2A, J61.2B, J67.2, J72.3, R130.1, U26.33, U30.8
ESP32_SDA5: J76.2A, J76.2B, J82.2, J87.3, R160.1, U32.33, U36.8
ESP32_SDA6: J91.2A, J91.2B, J97.2, J102.3, R190.1, U38.33, U42.8
ESP32_SDA7: J106.2A, J106.2B, J112.2, J117.3, R220.1, U44.33, U48.8
ESP32_SDA8: J121.2A, J121.2B, J127.2, J132.3, R250.1, U50.33, U54.8
ESP32_SDA9: J136.2A, J136.2B, J142.2, J147.3, R280.1, U56.33, U60.8
ESP32_TXD0: J7.2, J8.2, LED_TX.1, U1.35, U2.3
ESP32_TXD1: J18.2, J25.2, LED_TX1.1, U7.3, U8.35
ESP32_TXD2: J33.2, J40.2, LED_TX2.1, U13.3, U14.35
ESP32_TXD3: J48.2, J55.2, LED_TX3.1, U19.3, U20.35
ESP32_TXD4: J63.2, J70.2, LED_TX4.1, U25.3, U26.35
ESP32_TXD5: J78.2, J85.2, LED_TX5.1, U31.3, U32.35
ESP32_TXD6: J93.2, J100.2, LED_TX6.1, U37.3, U38.35
ESP32_TXD7: J108.2, J115.2, LED_TX7.1, U43.3, U44.35
ESP32_TXD8: J123.2, J130.2, LED_TX8.1, U49.3, U50.35
ESP32_TXD9: J138.2, J145.2, LED_TX9.1, U55.3, U56.35
GND: C1.2, C2.2, C3.2, C4.2, C5.2, C6.-, C7.2, C8.2, C9.-, C10.-, C11.2, C12.2, C13.2, C14.2, C15.2, C16.2, C17.2, C18.2, C19.2, D7.GND, DOOT.1, DOOT.2, J1.GND, J2.GND, J2.GND2, J3.GND, J4.3, J4.5, J4.7, J4.9, J5.4, J6.4A, J6.4B, J9.6, J9.7, J10.6, J10.7, J13.1, J15.6, J15.10, J15.11, J15.12, J15.13, J16.2, JP2.1, LED_18.1, LED_PWR.1, Q2.1, Q2.4, R2.1, R3.1, R11.1, R15.1, R16.1, R17.1, R18.1, R19.1, R20.1, R22.1, R24.1, R25.1, R26.1, R27.1, S1.1, S1.2, SHLD.1, U1.1, U1.15, U1.38, U1.GND, U1.GNDT1, U1.GNDT2, U1.GNDT3, U1.GNDT4, U1.GNDT5, U1.GNDT6, U1.GNDT7, U1.GNDT8, U2.1, U4.2, U5.2, U6.1, U6.4, U6.6, U6.9
GND2: C20.2, C21.2, C22.-, C23.2, C24.2, C25.2, C26.2, C27.2, C28.-, C29.2, C30.-, C31.2, C32.2, C33.2, C34.2, C35.2, C36.2, C37.2, C38.2, D14.GND, DOOT1.1, DOOT1.2, J14.4A, J14.4B, J17.6, J17.7, J20.GND, J20.GND2, J21.GND, J22.4, J23.6, J23.7, J26.3, J26.5, J26.7, J26.9, J27.1, J28.6, J28.10, J28.11, J28.12, J28.13, J29.GND, J30.2, JP19.1, LED_1.1, LED_PWR1.1, Q17.1, Q17.4, R33.1, R34.1, R41.1, R43.1, R44.1, R48.1, R49.1, R50.1, R51.1, R53.1, R54.1, R55.1, R56.1, R57.1, S2.1, S2.2, SHLD1.1, U7.1, U8.1, U8.15, U8.38, U8.GND, U8.GNDT1, U8.GNDT2, U8.GNDT3, U8.GNDT4, U8.GNDT5, U8.GNDT6, U8.GNDT7, U8.GNDT8, U10.2, U11.2, U12.1, U12.4, U12.6, U12.9
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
